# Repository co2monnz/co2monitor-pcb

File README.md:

# co2mon.nz Ventilation Monitor

Inspired by https://github.com/oseiler2/CO2Monitor

## Description

This is a prototype CO2 based ventilation monitor intended for fixed
(wall-mounted) use in standard residential, office and retail type spaces. It
uses the well regards Sensirion SCD40 CO2 sensor as well as a Bosch BME680 for
VOC and barometric pressure measurement and a Sensirion SHT30 for temperature
and humidity.

WiFi connectivity is provided by the main ESP32-S3 processor allowing
measurements to be reported back to the https://co2mon.nz/ web service if
desired.

An accompanying 3D printable case design can be found in the
https://github.com/co2monnz/cad repository.

## License, Copyright and Reuse

© 2023 [MKMBA Ltd](https://www.mkmba.nz/).

The design files (e.g. schematics, pcb layout and associated data) in this
repository are available under the terms of the CC-BY-NC license detailed in
the accompanying LICENSE file. 

There doesn't seem to be any perfect way of licensing hadware designs that I've
found yet, so if the CC-BY-NC terms are not suitable for you please get in
touch and I'll generally be fairly wiling to consider other options including
for commercial re-use, etc.

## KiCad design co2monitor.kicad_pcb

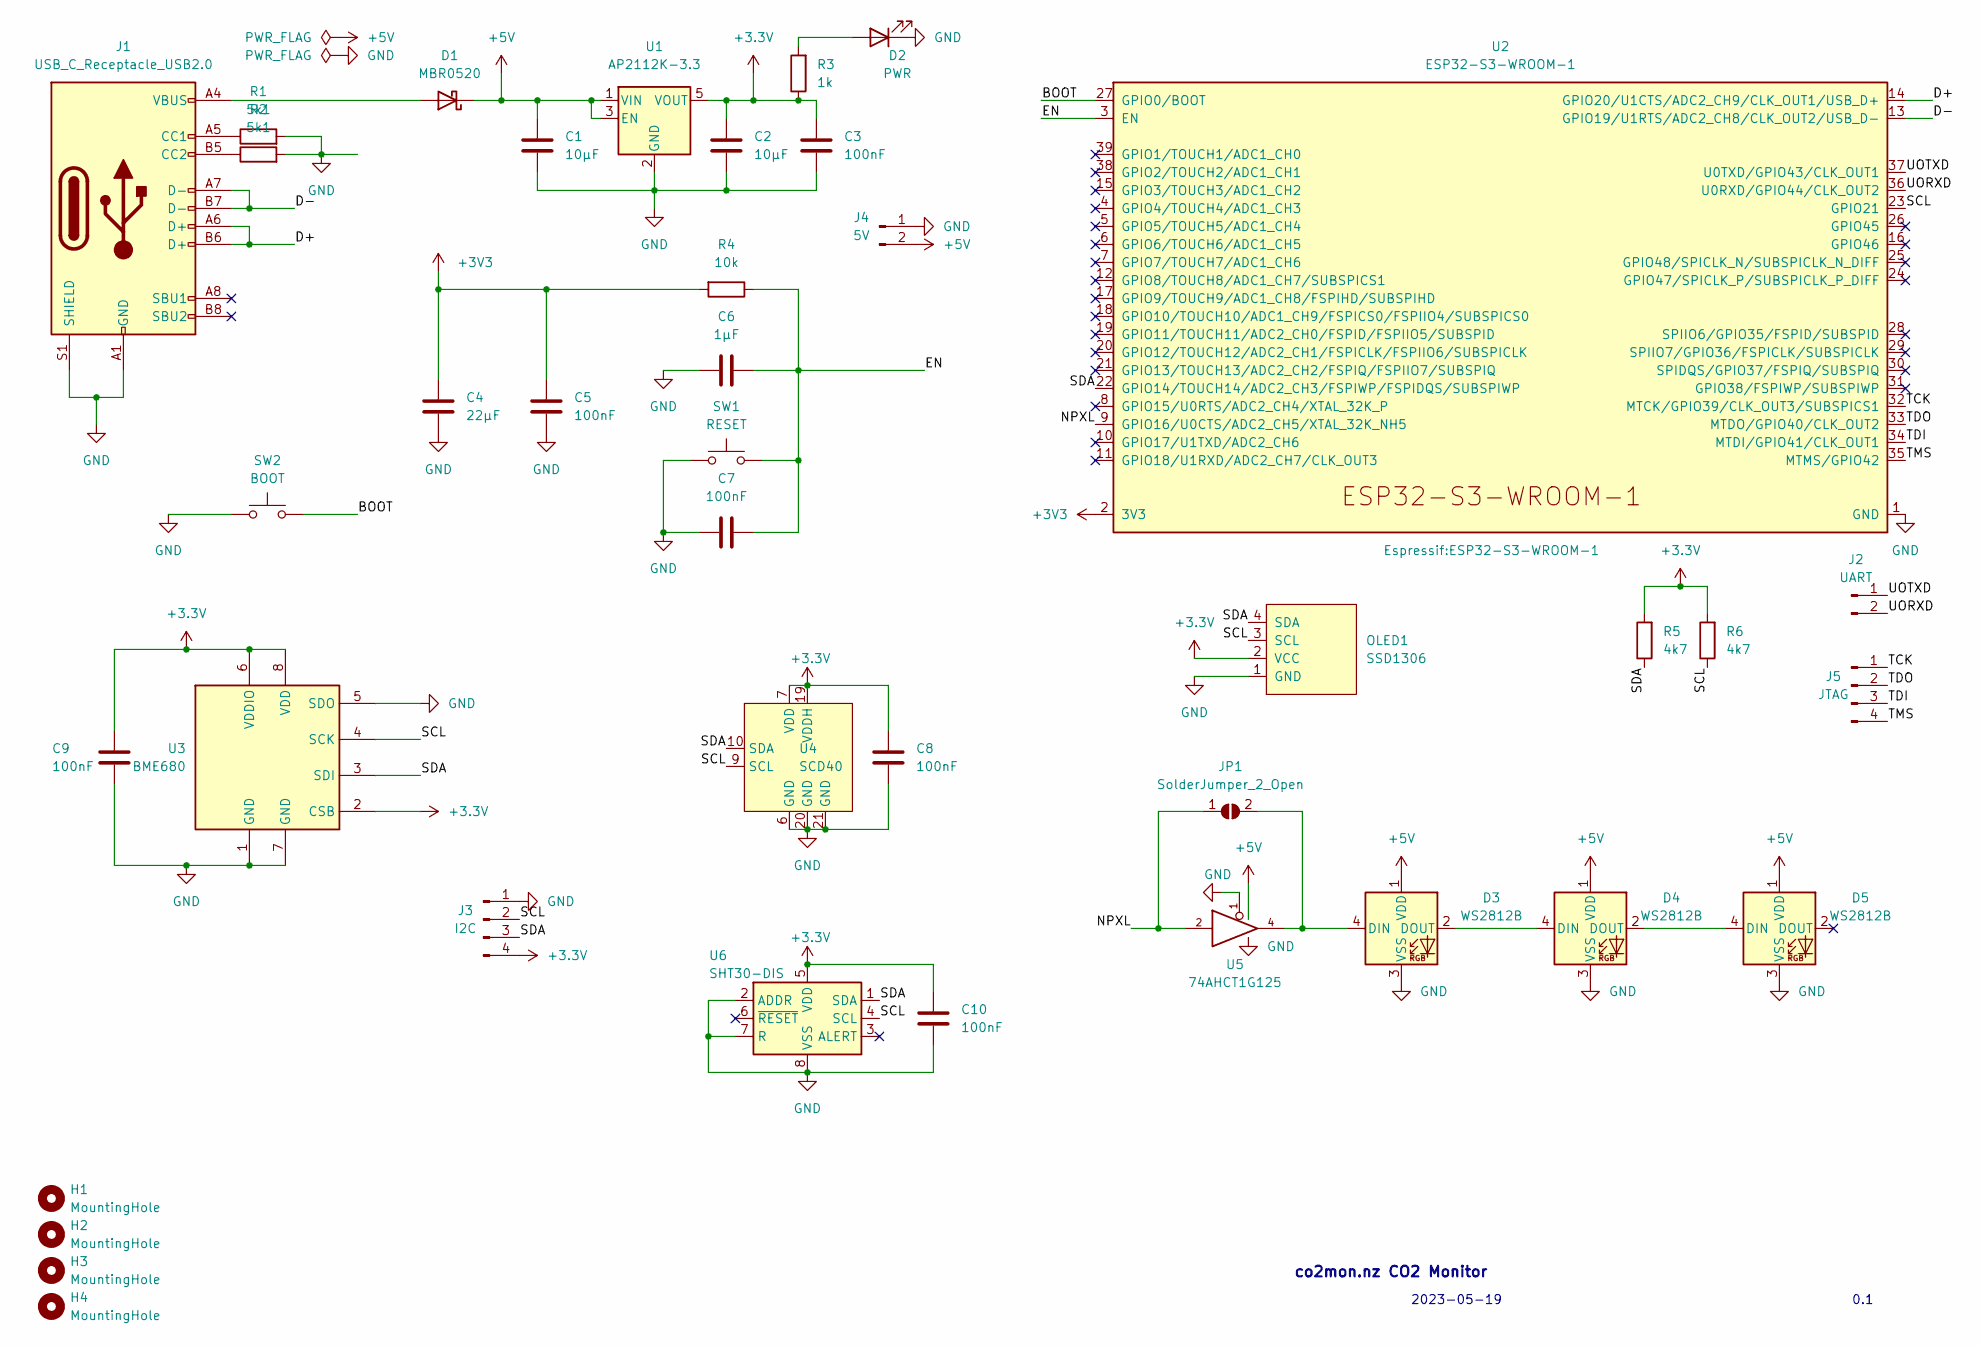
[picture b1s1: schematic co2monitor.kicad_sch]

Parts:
C1, C2: 10μF; C_0805_2012Metric; LCSC C15850
C3, C5, C7, C8, C9, C10: 100nF; C_0805_2012Metric; LCSC C14663
C4: 22μF; C_0805_2012Metric; LCSC C45783
C6: 1μF; C_0805_2012Metric; LCSC C28323
D1: MBR0520; D_SOD-123; LCSC C908230
D2: PWR; LED_0805_2012Metric; LCSC C84256
D3, D4, D5: WS2812B; LED_WS2812B_PLCC4_5.0x5.0mm_P3.2mm; MPN COM-16346; LCSC C2874885
H1, H2, H3, H4: MountingHole; MountingHole_3.5mm
J1: USB_C_Receptacle_USB2.0; USB_C_Receptacle_XKB_U262-16XN-4BVC11; LCSC C165948
J2: UART; PinHeader_1x02_P2.00mm_Vertical
J3: I2C; PinHeader_1x04_P2.00mm_Vertical
J4: 5V; PinHeader_1x02_P2.00mm_Vertical
J5: JTAG; PinHeader_1x04_P2.00mm_Vertical
JP1: SolderJumper_2_Open; SolderJumper-2_P1.3mm_Open_TrianglePad1.0x1.5mm
OLED1: SSD1306; OLED_128x64_0.96_small
R1, R2: 5k1; R_0805_2012Metric; LCSC C27834
R3: 1k; R_0805_2012Metric; LCSC C17513
R4: 10k; R_0805_2012Metric; LCSC C17414
R5, R6: 4k7; R_0805_2012Metric; LCSC C17673
SW1: RESET; SW_Push_1P1T_NO_CK_KMR2; LCSC C269272
SW2: BOOT; SW_Tactile_SPST_Angled_PTS645Vx83-2LFS; LCSC C221893
U1: AP2112K-3.3; SOT-23-5; LCSC C51118
U2: ESP32-S3-WROOM-1; LCSC C2913198
U3: BME680; Bosch_LGA-8_3x3mm_P0.8mm_ClockwisePinNumbering
U4: SCD40; SCD40-D-R1
U5: 74AHCT1G125; SOT-23-5; LCSC C7484
U6: SHT30-DIS; SHT30_DFN-8-1EP_2.5x2.5mm_P0.5mm_EP1.1x1.7mm; LCSC C77361

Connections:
+5V: C1.2, D1.1 (K), D3.1 (VDD), D4.1 (VDD), D5.1 (VDD), J4.2, U1.1 (VIN), U1.3 (EN), U5.5 (VCC)
/BOOT: SW2.2, U2.27 (GPIO0/BOOT)
/D+: J1.A6 (D+), J1.B6 (D+), U2.14 (GPIO20/U1CTS/ADC2_CH9/CLK_OUT1/USB_D+)
/D-: J1.A7 (D-), J1.B7 (D-), U2.13 (GPIO19/U1RTS/ADC2_CH8/CLK_OUT2/USB_D-)
/EN: C6.1, C7.2, R4.1, SW1.2, U2.3 (EN)
/NPXL: JP1.1 (A), U2.9 (GPIO16/U0CTS/ADC2_CH5/XTAL_32K_NH5), U5.2
/SCL: J3.2, OLED1.3 (SCL), R6.1, U2.23 (GPIO21), U3.4 (SCK), U4.9 (SCL), U6.4 (SCL)
/SDA: J3.3, OLED1.4 (SDA), R5.1, U2.22 (GPIO14/TOUCH14/ADC2_CH3/FSPIWP/FSPIDQS/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), U3.3 (SDI), U4.10 (SDA), U6.1 (SDA)
/TCK: J5.1, U2.32 (MTCK/GPIO39/CLK_OUT3/SUBSPICS1)
/TDI: J5.3, U2.34 (MTDI/GPIO41/CLK_OUT1)
/TDO: J5.2, U2.33 (MTDO/GPIO40/CLK_OUT2)
/TMS: J5.4, U2.35 (MTMS/GPIO42)
/UORXD: J2.2, U2.36 (U0RXD/GPIO44/CLK_OUT2)
/UOTXD: J2.1, U2.37 (U0TXD/GPIO43/CLK_OUT1)
GND: C1.1, C2.1, C3.2, C4.1, C5.2, C6.2, C7.1, C8.1, C9.1, C10.1, D2.1 (K), D3.3 (VSS), D4.3 (VSS), D5.3 (VSS), J1.A1 (GND), J1.A12 (GND), J1.B1 (GND), J1.B12 (GND), J1.S1 (SHIELD), J3.1, J4.1, OLED1.1 (GND), R1.2, R2.2, SW1.1, SW2.1, U1.2 (GND), U2.1 (GND), U2.40 (GND), U2.41 (GND), U3.1 (GND), U3.5 (SDO), U3.7 (GND), U4.6 (GND), U4.20 (GND), U4.21 (GND), U5.1, U5.3 (GND), U6.2 (ADDR), U6.7 (R), U6.8 (VSS), U6.9 (VSS)
unnamed: D1.2 (A), J1.A4 (VBUS), J1.A9 (VBUS), J1.B4 (VBUS), J1.B9 (VBUS)
unnamed: D2.2 (A), R3.2
unnamed: D3.2 (DOUT), D4.4 (DIN)
unnamed: D3.4 (DIN), JP1.2 (B), U5.4
unnamed: D4.2 (DOUT), D5.4 (DIN)
unnamed: J1.A5 (CC1), R1.1
unnamed: J1.B5 (CC2), R2.1

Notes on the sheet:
co2mon.nz CO2 Monitor
0.1
2023-05-19

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
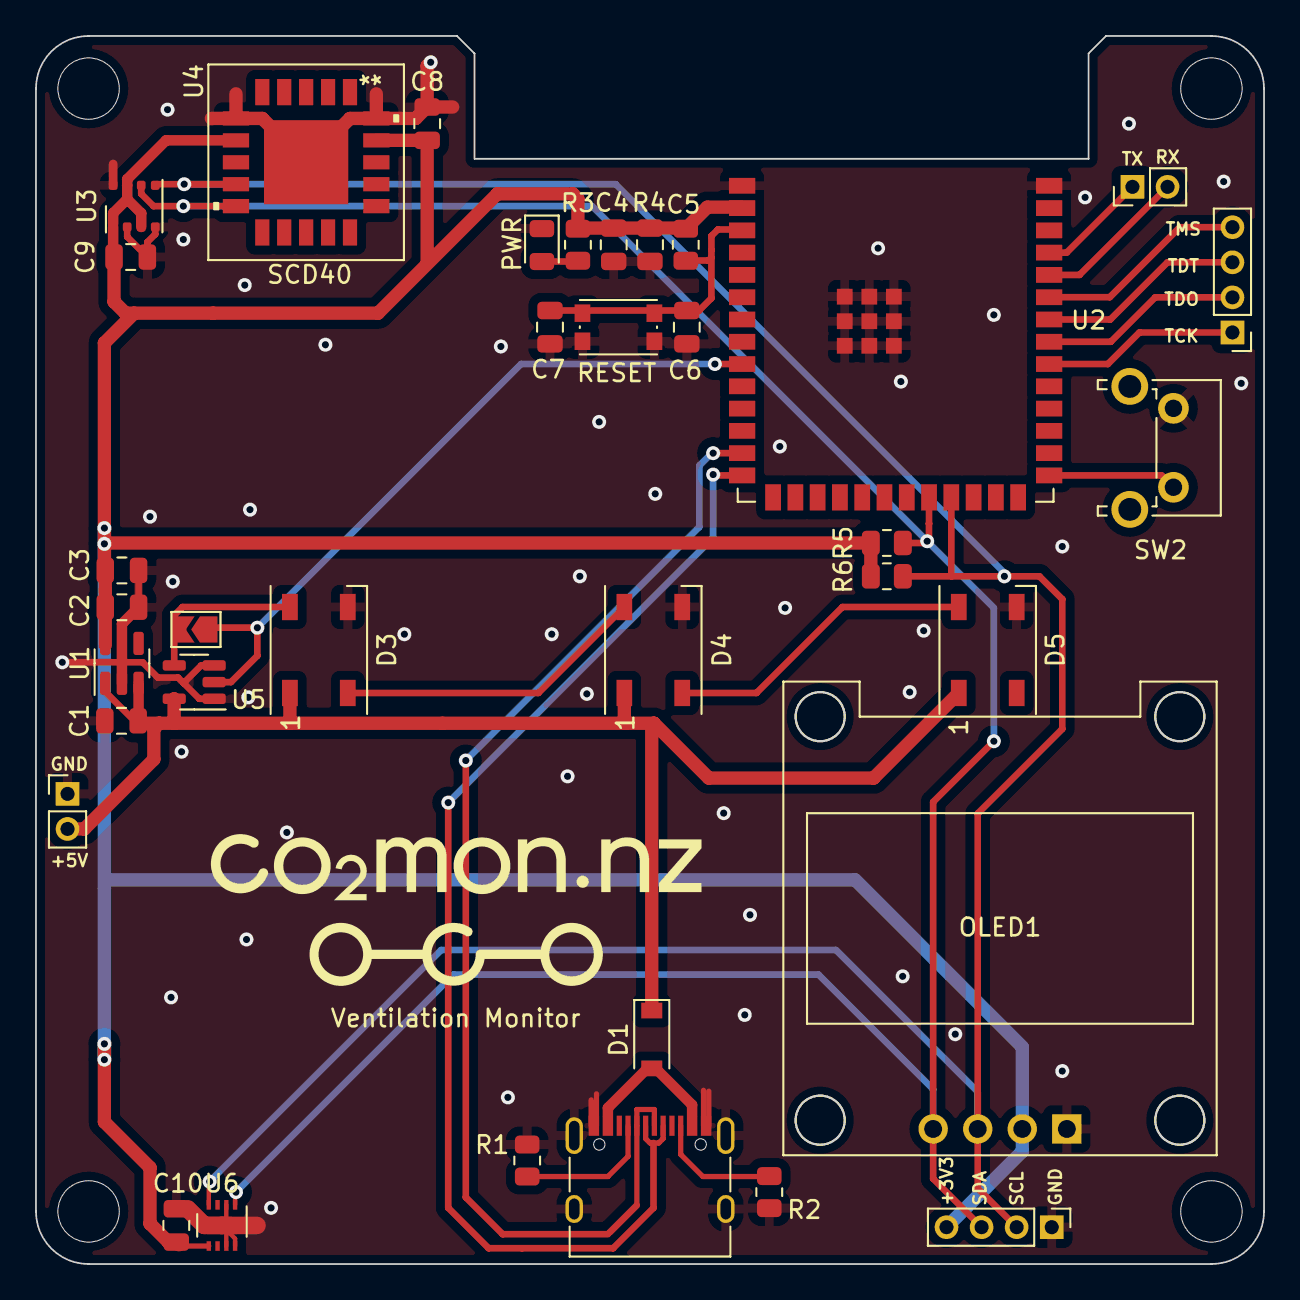
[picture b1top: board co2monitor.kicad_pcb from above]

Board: 2 copper layers, 70.0 x 70.0 mm, 40 parts (0 on the bottom side), 23 nets.

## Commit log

2023-05-20 Initial draft design.
    No idea if this will work :)
2023-05-21 Attempt #2
    - Larger board (aesthetics)
    - Add SHT30 for more accurate temperature measurements
    - Larger tracks
2023-05-21 Add logo
2023-05-21 Fix neopixel pinout/footprint
    Turns out the NEOPIXEL_THT and WS2812B symbols have differing pinouts,
    the WS2812B one appears to match reality, which required a slight
    re-layout once the associated footprint changed.
    Also fixed/enlarged a few ground tracks in the power-supply noticed
    while inspecting the new area fills.
    Credit to oseiler2 for spotting the pinout issue.
2023-05-21 Add .gitignore missing from original commit!
2023-05-21 Tweak a few more ground tracks
2023-05-21 Break out various signals to debugging headers
2023-05-21 Flip the screen for better positioning.
2023-05-21 use the mounting holes in the footprint
    We don't need to duplicate these ourselves!
2023-05-21 Add JTAG header
2023-05-21 Don't silkscreen "Antenna Area" outside board
2023-05-21 Fix oled text orientation
2023-05-21 Fix undersized boot button track
2023-05-21 Ignore JLCPCB Tools plugin files
2023-05-22 Prepare for fabrication at JLCPCB
    - Assign LCSC part numbers
    - Add copyright/version/order no placeholder to back silkscreen
2023-05-22 -N4 not -N8 WROOM
2023-05-22 Add basic README and LICENSE
    Licensing hardware designs seems hard to do perfectly... CC-BY-NC seems
    like a reasonable choice for now.
2023-06-13 Add link to case design.
